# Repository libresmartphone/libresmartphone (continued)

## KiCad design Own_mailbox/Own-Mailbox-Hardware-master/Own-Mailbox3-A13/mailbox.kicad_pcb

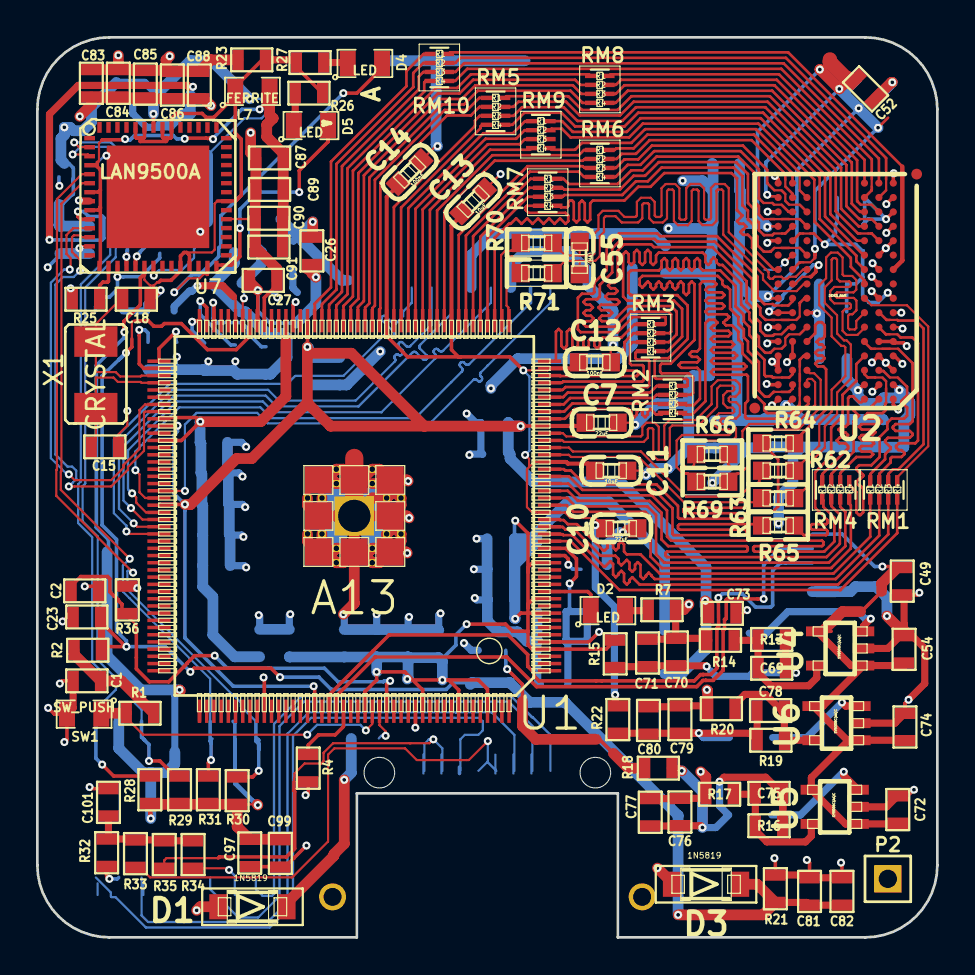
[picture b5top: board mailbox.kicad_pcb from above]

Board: 4 copper layers, 50.0 x 50.0 mm, 183 parts (0 on the bottom side), 171 nets.

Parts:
C1, C16, C17, C19, C20, C21: 1nF; SM0603
C2, C4, C5, C8, C9, C27, C29, C30, C31, C32, C33, C34, C35, C36, C37, C38, C40, C41, C42, C43, C44, C45, C46, C47, C48, C50, C51, C53, C56, C57, C58, C59, C61, C62, C83, C84, C85, C86, C87, C88, C89, C90, C91, C92, C96, C97, C98, C99, C100, C102: 100nF; SM0603
C3, C6, C23, C39, C49, C52, C54, C60, C65, C70, C71, C72, C74, C76, C77, C79, C80, C81, C82: 22uF; SM0603
C7, C10: 22uF; C0603_DWS
C11, C13: 10uF; C0603_DWS
C12, C14: 100nF; C0603_DWS
C15, C18, C94, C95: 10pF; SM0603
C22, C93, C101: 1uF; SM0603
C24, C26, C28, C63, C64, C66, C67, C68, C73: 10uF; SM0603
C25: C; SM0603
C55: (NA); C0603_DWS
C69, C78: 22pF; SM0603
C75: 47pF; SM0603
D1, D3: 1N5819; SOD-123
D2, D4, D5: LED; SM0805
L1: 420nH; SM0805
L3, L4, L5, L6: 2.2uH; CD32
L7, L8, L9: FERRITE; SM0805
P1: CONN_4; CONN_USB_MINI_PIERRE
P2: CONN_1; PIN_ARRAY_1
P3: CONN_8; RJ45_LP_RA_SMT
R1: 6.8k(1%); SM0603
R2: 100k (1%); SM0603
R3, R4: 47k; SM0603
R5, R6, R13: 2k(1%); SM0603
R7: 500R; SM0603
R8: 240R; SM0603
R9: 200k(1%); SM0603
R10, R11: 1k(1%); SM0603
R12: 240R(1%); SM0603
R14: 1.5k(1%); SM0603
R15, R18, R22, R23: 0R; SM0603
R16: 100k(1%); SM0603
R17: 22k(1%); SM0603
R19: 4.99k(1%); SM0603
R20: 3.3k(1%); SM0603
R21: 2.2k; SM0603
R24, R25: 12k; SM0603
R26, R27: 100R; SM0603
R28, R29, R30, R31: 50R; SM0603
R32, R33, R34, R35: 75R; SM0603
R36: 10k; SM0603
R62, R63, R64, R65, R66, R69, R70, R71: 22R; R0603_5MIL_DWS
RM1, RM2, RM3, RM7: 22Rx4; R_MATRIX_4_0402_25X625
RM4, RM5, RM6, RM8, RM9, RM10: 22RX4; R_MATRIX_4_0402_25X625
SW1: SW_PUSH; SM0805
T1: ETH10_00_transfo; H1601CG
U1: A13; TQFP176
U2: DDR3_RAM; FBGA96
U3: CONN_microSD; Memory_Card_microSD_DM3CS-SF
U4, U5, U6: SY8008C(AA)C; SOT23-5
U7: LAN9500A; QFN48
X1: CRYSTAL; SMDXTAL24mhz
X2: CRYSTAL_SMD2; Xtal25Mhz

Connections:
1V5: C4.1, C10.1, C11.1, C12.1, C13.1, C14.1, C30.1, C31.1, C32.1, C33.1, C34.1, C35.1, C36.1, C37.1, C38.1, C39.1, C40.1, C41.1, C42.1, C43.1, C44.1, C45.1, C46.1, C47.1, C52.1, R5.1, R11.1, R22.1, U1.23, U1.30, U1.43, U1.53, U1.62, U2.A1, U2.A8, U2.B2, U2.C1, U2.C9, U2.D2, U2.D9, U2.E9, U2.F1, U2.G7, U2.H2, U2.H9, U2.K2, U2.K8, U2.N1, U2.N9, U2.R1, U2.R9
3V3ETH: C97.2, C99.1, L7.1, R23.1, R26.2, R27.2, R28.1, R29.1, R30.2, R31.2, T1.2, T1.7, U7.20, U7.24, U7.25, U7.35, U7.48, U7.49, U7.51, U7.52
3VA: C23.2, C81.1, C82.1, D3.2, R2.1, R21.1, U1.81
+5V: C49.1, C54.1, C72.1, C74.1, P1.1, U4.1, U4.4, U5.1, U5.4, U6.1, U6.4
/Erhernet/RX+: P3.7, T1.11
/Erhernet/RX-: P3.8, T1.9
/Erhernet/TX+: P3.3, T1.16
/Erhernet/TX-: P3.6, T1.14
DDR3_A00: RM5.1.2, U2.N3
DDR3_A01: RM6.3.2, U2.P7
DDR3_A02: RM8.3.2, U2.P3
DDR3_A03: RM8.4.2, U2.N2
DDR3_A04: RM6.4.2, U2.P8
DDR3_A05: RM8.2.2, U2.P2
DDR3_A06: RM6.2.2, U2.R8
DDR3_A07: RM10.2.2, U2.R2
DDR3_A08: RM6.1.2, U2.T8
DDR3_A09: RM10.4.2, U2.R3
DDR3_A10: RM7.3.2, U2.L7
DDR3_A11: RM9.4.2, U2.R7
DDR3_A12: RM7.1.2, U2.N7
DDR3_A13: RM8.1.2, U2.T3
DDR3_BA0: RM5.2.2, U2.M2
DDR3_BA1: RM7.2.2, U2.N8
DDR3_BA2: RM5.3.2, U2.M3
DDR3_CAS: RM9.1.2, U2.K3
DDR3_CKE: RM7.4.2, U2.K9
DDR3_CK_N: C55.2, R70.1, U2.K7
DDR3_CK_P: C55.1, R71.1, U2.J7
DDR3_D00: RM1.1.2, U2.E3
DDR3_D01: RM3.4.2, U2.F7
DDR3_D02: RM1.2.2, U2.F2
DDR3_D03: RM3.3.2, U2.F8
DDR3_D04: RM1.4.2, U2.H3
DDR3_D05: RM3.1.2, U2.H8
DDR3_D06: RM1.3.2, U2.G2
DDR3_D07: RM3.2.2, U2.H7
DDR3_D08: RM2.3.2, U2.D7
DDR3_D09: RM4.3.2, U2.C3
DDR3_D10: RM2.1.2, U2.C8
DDR3_D11: RM4.4.2, U2.C2
DDR3_D12: RM2.4.2, U2.A7
DDR3_D13: RM4.2.2, U2.A2
DDR3_D14: RM2.2.2, U2.B8
DDR3_D15: RM4.1.2, U2.A3
DDR3_DM0: R64.2, U2.E7
DDR3_DM1: R65.2, U2.D3
DDR3_DQS0_N: R62.2, U2.G3
DDR3_DQS0_P: R63.2, U2.F3
DDR3_DQS1_N: R66.1, U2.B7
DDR3_DQS1_P: R69.1, U2.C7
DDR3_ODT: RM10.1.2, U2.K1
DDR3_RAS: RM9.2.2, U2.J3
DDR3_RST: RM10.3.2, U2.T2
DDR3_WE: RM5.4.2, U2.L3
GND: C1.2, C2.2, C3.2, C5.2, C6.2, C7.2, C8.2, C9.1, C10.2, C11.2, C12.2, C13.2, C14.2, C15.1, C16.1, C17.1, C18.1, C19.1, C20.1, C21.1, C22.1, C23.1, C24.1, C25.1, C26.1, C27.1, C28.1, C29.1, C30.2, C31.2, C32.2, C33.2, C34.2, C35.2, C36.2, C37.2, C38.2, C39.2, C40.2, C41.2, C42.2, C43.2, C44.2, C45.2, C46.2, C48.2, C49.2, C50.2, C51.2, C52.2, C53.2, C54.2, C56.2, C57.2, C58.2, C59.2, C60.2, C61.2, C62.2, C63.2, C64.2, C65.2, C66.2, C67.2, C68.2, C70.2, C71.2, C72.2, C73.2, C74.2, C76.2, C77.2, C79.2, C80.2, C81.2, C82.2, C83.2, C84.2, C85.2, C86.2, C87.2, C88.2, C89.2, C90.2, C91.2, C92.2, C93.2, C94.1, C95.1, C96.2, C97.1, C98.2, C99.2, C100.2, C101.1, C102.1, P1.4, P2.1, R6.2, R7.2, R8.2, R9.1, R10.2, R12.2, R14.2, R17.2, R20.2, R21.2, R24.1, R25.1, SW1.2, U1.79, U1.177, U2.A9, U2.B1, U2.B3, U2.B9, U2.D1, U2.D8, U2.E1, U2.E2, U2.E8, U2.F9, U2.G1, U2.G8, U2.G9, U2.J2, U2.J8, U2.L2, U2.M1, U2.M9, U2.P1, U2.P9, U2.T1, U2.T9, U3.6, U3.9, U4.2, U5.2, U6.2, U7.13, U7.33, X2.2, X2.4
LED1: D4.2, U7.27
LED2: D5.2, U7.28
unnamed: C1.1, R1.1, R2.2
unnamed: C2.1, R36.1, U1.159
unnamed: C6.1, L1.2, U3.4
unnamed: C16.2, U1.90
unnamed: C17.2, U1.89
unnamed: C19.2, U1.88
unnamed: C20.2, U1.87
unnamed: C21.2, U1.86
unnamed: C22.2, U1.83
unnamed: C26.2, C27.2, U1.80
unnamed: C28.2, C29.2, R9.2, U1.82
unnamed: C47.2, C48.1, R10.1, R11.2, U2.H1, U2.M8
unnamed: C69.1, C70.1, C71.1, L3.2, R13.1, R15.2
unnamed: C69.2, R13.2, R14.1, U4.5
unnamed: C75.1, C76.1, C77.1, L5.2, R16.1, R18.2
unnamed: C75.2, R16.2, R17.1, U5.5
unnamed: C78.1, C79.1, C80.1, L6.2, R19.1, R22.2
unnamed: C78.2, R19.2, R20.1, U6.5
unnamed: C94.2, U7.19, X2.3
unnamed: C95.2, U7.18, X2.1
unnamed: C101.2, R32.1, R33.1, R34.1, R35.1
unnamed: C24.2, C102.2, U1.75
unnamed: D1.2, R3.1
unnamed: D2.1, U1.12
unnamed: D2.2, R7.1
unnamed: D4.1, R27.1
unnamed: D5.1, R26.1
unnamed: L3.1, U4.3
unnamed: L5.1, U5.3
unnamed: L6.1, U6.3
unnamed: P3.1, P3.2, R35.2
unnamed: P3.4, P3.5, R33.2
unnamed: R3.2, U1.158
unnamed: R4.1, U1.153
unnamed: R8.1, U1.17
unnamed: R12.1, U2.L8
unnamed: R24.2, U7.8
unnamed: R25.2, U7.16
unnamed: R32.2, T1.15
unnamed: R34.2, T1.10
unnamed: R62.1, U1.32
unnamed: R63.1, U1.31
unnamed: R64.1, U1.29
unnamed: R65.1, U1.28
unnamed: R66.2, U1.34
unnamed: R69.2, U1.33
unnamed: R70.2, U1.46
unnamed: R71.2, U1.45
unnamed: RM1.1.1, U1.22
unnamed: RM1.2.1, U1.21
unnamed: RM1.3.1, U1.20
unnamed: RM1.4.1, U1.19
unnamed: RM2.1.1, U1.39
unnamed: RM2.2.1, U1.38
unnamed: RM2.3.1, U1.37
unnamed: RM2.4.1, U1.36
unnamed: RM3.1.1, U1.44
unnamed: RM3.2.1, U1.42
unnamed: RM3.3.1, U1.41
unnamed: RM3.4.1, U1.40
unnamed: RM4.1.1, U1.27
unnamed: RM4.2.1, U1.26
unnamed: RM4.3.1, U1.25
unnamed: RM4.4.1, U1.24
unnamed: RM5.1.1, U1.64
unnamed: RM5.2.1, U1.63
unnamed: RM5.3.1, U1.61
unnamed: RM5.4.1, U1.60
unnamed: RM6.1.1, U1.55
unnamed: RM6.2.1, U1.54
unnamed: RM6.3.1, U1.52
unnamed: RM6.4.1, U1.51
unnamed: RM7.1.1, U1.50
unnamed: RM7.2.1, U1.49
unnamed: RM7.3.1, U1.48
unnamed: RM7.4.1, U1.47
unnamed: RM8.1.1, U1.68
unnamed: RM8.2.1, U1.67
unnamed: RM8.3.1, U1.66
unnamed: RM8.4.1, U1.65
unnamed: RM9.1.1, U1.59
unnamed: RM9.2.1, U1.58
unnamed: RM9.3.1, U1.57
unnamed: RM9.4.1, U1.56
unnamed: RM10.1.1, U1.72
unnamed: RM10.2.1, U1.71
unnamed: RM10.3.1, U1.70
unnamed: RM10.4.1, U1.69
RPX_N: R30.1, T1.8, U7.5
RPX_P: R31.1, T1.6, U7.6
SDC0_CLK: U1.110, U3.5
SDC0_CMD: U1.111, U3.3
SDC0_D0: U1.108, U3.7
SDC0_D1: U1.107, U3.8
SDC0_D2: U1.113, U3.1
SDC0_D3: U1.112, U3.2
SVREF: C4.2, C5.1, C8.1, R5.2, R6.1, U1.18
TPX_N: R29.2, T1.3, U7.2
TPX_P: R28.2, T1.1, U7.3
UART1_RX: P1.3, U1.151
UART1_TX: P1.2, U1.152
UBOOT: R1.2, SW1.1, U1.157
USB_ETH_N: U1.95, U7.11
USB_ETH_P: U1.96, U7.12
VCC: C3.1, C9.2, C25.2, C50.1, C56.1, C57.1, C60.1, C83.1, C84.1, C85.1, C86.1, C88.1, D1.1, D3.1, L1.1, R4.2, R18.1, R23.2, R36.2, U1.5, U1.76, U1.97, U1.100, U1.142, U1.163
VDD33A: C87.1, C89.1, C90.1, C91.1, L7.2, U7.4, U7.7, U7.9, U7.15
VDDBUSPLL: C92.1, L8.2, U7.17
VDDCORE: C93.1, C96.1, C98.1, L8.1, L9.1, U7.21, U7.50
VDDPLL: C100.1, L9.2, U7.10
VDD_CPU: C51.1, C58.1, C61.1, C62.1, C65.1, C66.1, C67.1, C68.1, L4.1, R15.1, U1.4, U1.9, U1.11, U1.16, U1.156, U1.164, U1.169, U1.173
VDD_INT: C7.1, C53.1, C59.1, C63.1, C64.1, C73.1, L4.2, U1.35, U1.73, U1.98, U1.109, U1.149
X1_N: C15.2, U1.92, X1.1
X1_P: C18.2, U1.91, X1.2

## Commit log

2015-04-20 Add Readme.txt
2015-04-20 Add kkc.py
2015-04-20 Add kk6c.py and kkh1.py
2015-04-20 Add multiplebutton2.py
2015-04-20 Add multiplebutton4.py
2015-04-21 Add multiplebutton6.py
2015-06-14 remove old files
2015-06-14 GTA02-MB-A6 contains the PCB layout in original PADS, Gerber and PDF formats.
2015-06-27 License
2015-06-28 libresmartphone software v0.1
2015-08-25 libresmartphone v0.2
    newer version of libresmartphone.
    Automatic port connection.
    Better coding
2015-08-30 Update of libresmartphone software
    Changes in this version of libresmartphone:
    · Pull calls.
    · Read SMS.
    · Level of battery.
2015-09-16 In this update (v0.3.1) The libresmartphone software can send SMS.
2015-09-20 Libresmartphone software v0.3.2. Changes: · Virtual keyboard in the sms tab.
2015-09-21 Camera software v0.1
2016-02-05 Librecalc files
2016-02-05 Own-mailbox files
2016-02-05 Neo900
2016-02-05 Manga Screen
2016-02-05 Udoo Neo http://udoo.org/download/files/schematics/
2016-02-22 Make two folders
2016-02-22 New folder
2016-02-25 Freecalypso
2016-03-14 Create New_folder
2016-03-15 SMS keyboard shows capital letters
2016-04-19 change teditdis to teditdisp in global
2016-08-07 Create OpenPandora
2016-09-24 Modify open pandora
2016-09-24 open pandora modification
2016-09-25 modify folders
2017-04-30 Move to older versions
2017-04-30 Rename Libresmartphone/Libresmartphone Software/libresmartphone_v0.3.3.py to Libresmartphone/Libresmartphone Software/Older_versions/libresmartphone_v0.3.3.py
2017-04-30 Updated without the need of connecting an arduino.
2017-04-30 Rename Libresmartphone/Libresmartphone Software/modular_private_smartphone_v0.4.0.py to Libresmartphone/Libresmartphone Software/Modular_private_smartphone_v0.4/modular_private_smartphone_v0.4.0.py
2017-04-30 Improving README
2017-05-01 Update README.md
    Add bank account and mail
2017-05-02 Update README.md
    Change and to an in line 56
2017-06-28 Zerophone addition
    Add Zerophone to other projects
2017-06-28 Update other projects with zerophone
